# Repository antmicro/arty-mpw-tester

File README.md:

# Arty MPW Tester

Copyright (c) 2022-2025 [Antmicro](https://www.antmicro.com)

### Overview

This repository contains open hardware design files for a simple expansion board compatible with [Digilent Arty A7](https://digilent.com/shop/arty-a7-artix-7-fpga-development-board/) development kit.
This board connects IO signals from the Xilinx Artix FPGA located on the Arty board to an open hardware [Caravel](https://github.com/efabless/caravel_board) breakout board.
The Caravel breakout board allows testing ASIC designs prepared for Multi Project Wafer (MPW) shuttles and fabricated with one of the available open Process Design Kits (PDKs).

You can learn more about Open Shuttle Program by visiting this [link](https://efabless.com/open_shuttle_program).

The Arty MPW Tester board routes the interfaces from Caravel and provides the necessary power buses.
The design files were prepared in KiCad 9.

## Repository structure

The main repository directory contains KiCad PCB project files, a [LICENSE](LICENSE), and a README.
The remaining files are stored in the following directories:

* `doc` - contains generated documentation
* `img` - contains graphics for this README

## Key features

* Caravel-breakout testbed slot with optional FlexyPins
* Arty A7 chipKIT compatible
* USB for MPRJ SPI/UART debug
* SPI Flash connected to Caravel and Arty
* Dedicated 10MHz oscillator
* Dual LDO with fixed and I2C controlled feedback (selectable)
* 37 MPRJ_IO, clock input, GPIO and reset connected to chipKIT header
* Pin headers for all power rails, reset, clock, UART and SPI Flash

## Licensing

This project is published under the [Apache-2.0](LICENSE) License.

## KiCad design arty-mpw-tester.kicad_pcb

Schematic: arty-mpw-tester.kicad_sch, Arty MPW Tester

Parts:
C1, C3, C22, C23, C24, C26, C27, C28, C29, C30, C31, C32, C35, C36: C_1u_0603; 0603-cap; MPN 0603YD105KAT2A
C2, C4, C19, C20, C21, C25, C33, C34, C37: C_100n_0603; 0603-cap; MPN 0603YC104KAZ2A
D3, D4: KP-1608ZGC; LED_0603; MPN KP-1608EC
D6, D9: PMEG6002EJ,115; SOD-323F; MPN PMEG6002EJ,115
D7, D8: 1N5819HW-7-F; SOD-123; MPN 1N5819HW-7-F
J3: arty_chipKIT_connector; ARTY_A7_SHIELD; MPN 9-146281-0
J4, J6, J7, J8, J9, J10, J11, J12: 61300211121; PinHeader_1x2_P2.54_Drill0.9mm; MPN 61300211121
J5, J14, J15: 61300311121; PinHeader_1x3_P2.54_Drill1.1mm; MPN 61300311121
J18, J20: 61300411121; PinHeader_1x4_P2.54mm_Drill1.02mm; MPN 61300411121
J19: 61300711121; MPN 61300711121
NT1, NT2, NT3, NT4, NT5, NT6, NT7, NT8, NT9, NT10, NT11, NT12, NT13, NT14: NetTie_2; NetTie-2_SMD_Pad0.15mm
Q1: DTC014TEBTL; SOT-416; MPN DTC014TEBTL
R1, R9, R10, R38, R39, R40, R41: R_0R01_1206; 1206-res; MPN RL1206FR-7W0R01L
R8, R11, R14, R15, R29, R35: R_0R_0603; 0603-res; MPN CR0603-J/-000ELF
R12, R13: R_470R_0603; 0603-res; MPN CR0603-JW-471GLF
R16, R17, R18, R19, R20, R21, R26, R28, R30, R32, R33, R34, R36, R37: R_10k_0603; 0603-res; MPN CR0603-JW-103ELF
R22: R_68k_0603; 0603-res; MPN MC0063W0603168K
R23: R_41k2_0603; 0603-res; MPN CRCW060341K2FKEA
R24: R_15k_0603; 0603-res; MPN CR0603-FX-1502ELF
R25: R_34k_0603; 0603-res; MPN ERJ-3EKF3402V
R27, R31: R_4k7_0603; 0603-res; MPN CR0603-FX-4701ELF
S1: KMR2; SW_SPST_4.2x2.8; MPN KMR211NGLFS
SW1, SW3: JS202011JCQN; MPN JS202011JCQN
TP1: RCW-0C; PROBE_PAD_1206; MPN RCW-0C
U1, U3: PAC1954T-E/4MX; VQFN-16-1EP_3x3mm_P0.5mm_EP1.1x1.1mm; MPN PAC1954T-E/4MX
U4: MAX811REUS+T; SOT-143-4; MPN MAX811REUS+T
U5: NTS0102DP; TSSOP-8_W3mm; MPN NTS0102DP
U6: MCP4661-103E/ML; QFN-16_EP_4x4_Pitch0.65mm; MPN MCP4661103E/ML
U7: Caravel_breakout_PCB_flexypin; caravel-breakout-flexypin
U8: W25Q32FVSS; SOIC127P790X216-8N; MPN W25Q32FVSSIG
U9: MIC2211-AAYML-TR; DFN-10-1EP_3x3mm; MPN MIC2211-AAYML-TR
Y2: ECS-2520MVLC-100-BN-TR; Oscillator_SMD_ECS_2520MV-xxx-xx-4Pin_2.5x2.0mm; MPN ECS-2520MVLC-100-BN-TR

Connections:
3V3_FTDI: C2.1, C4.1, R36.1, R37.1, U1.2 (VDD), U3.2 (VDD), U3.6 (ADDRSEL); also elsewhere on the board
+1V8: C36.1, J10.1, J11.1, J12.1, R24.2, R26.2, U9.9 (VOUT2)
+3V3: C19.1, C20.1, C34.1, C35.1, D3.1, D4.1, J6.1, J7.1, J8.1, J9.1, R16.2, R17.1, R18.1, R19.1, R21.1, R22.2, R28.1, R32.1, R34.1, U4.4 (VCC), U8.8 (VCC), U9.10 (VOUT1), Y2.4 (VDD)
/3V3_ARTY: C1.1, C21.1, J3.4 (3V3), U5.3 (VCC_A), U5.6 (OE)
/5V0: C25.1, C32.1, C37.1, D7.K, D8.K, R20.1, R27.2, R30.1, R31.2, R33.1, U5.7 (VCC_B), U6.15 (VDD), U9.1 (VIN)
/5V0_ARTY: C3.1, D8.A, J3.5 (5V), SW3.2 (1_C), SW3.6 (2_C)
/ARTY_EN_VOUT1: J3.9 (A0), SW1.1
/ARTY_EN_VOUT2: J3.19 (A6), SW1.5
/ARTY_MEM_CS: J3.25 (SS), R8.1
/ARTY_MEM_MISO: J3.28 (MISO), R14.1
/ARTY_MEM_MOSI: J3.29 (MOSI), R15.1
/ARTY_MEM_SCK: J3.27 (SCK), R11.1
/ARTY_SCL: R31.1, U5.8 (B1), U6.1 (SCL)
/ARTY_SCL_3V3: J3.47 (SCL), U1.4 (SM_CLK), U3.4 (SM_CLK), U5.5 (A1)
/ARTY_SDA: R27.1, U5.1 (B2), U6.2 (SDA)
/ARTY_SDA_3V3: J3.48 (SDA), U1.5 (SM_DATA), U3.5 (SM_DATA), U5.4 (A2)
/ARTY_XCLK: J3.32 (IO40), J5.3
/ARTY_~MR: D9.K, J3.31 (IO41)
/BYP: C33.1, U9.4 (BYP)
/CRVL_GPIO: J20.2, Q1.1 (B), R35.1, U7.47 (GPIO)
/CRVL_XCLK: J5.2, J20.3, U7.52 (XCLK)
/CRVL_~RST: J20.4, R34.2, U4.2 (~RST), U7.53 (~RST)
/EN_VOUT1: R33.2, SW1.2 (1_C), U9.2 (EN1)
/EN_VOUT2: R30.2, SW1.6 (2_C), U9.3 (EN2)
/HVC: R29.2, U6.16 (HVC/A0)
/LV_BOOSTER: J15.3, R26.1
/P0A: J14.2, R22.1, U6.8 (P0A)
/P0B: J14.1, R23.2, U6.10 (P0B)
/P0W: U6.9 (P0W), U9.5 (ADJ1)
/P1A: J15.2, R24.1, U6.7 (P1A)
/P1B: J15.1, R25.2, U6.5 (P1B)
/P1W: U6.6 (P1W), U9.7 (ADJ2)
/VCCD: C28.1, C31.1, NT12.2, R41.2, U7.6 (VCCD), U7.50 (VCCD)
/VCCD1: C24.1, NT13.2, R9.2, U7.43 (VCCD1)
/VCCD1_SEN_+: NT6.1, U3.11 (IN1+)
/VCCD1_SEN_-: NT13.1, U3.12 (IN1-)
/VCCD2: C22.1, NT14.2, R10.2, U7.56 (VCCD2)
/VCCD2_SEN_+: NT7.1, U3.13 (IN2+)
/VCCD2_SEN_-: NT14.1, U3.14 (IN2-)
/VCCD_SEN_+: NT5.1, U3.8 (IN3+)
/VCCD_SEN_-: NT12.1, U3.7 (IN3-)
/VDDA: C30.1, NT9.2, R38.2, U7.45 (VDDA)
/VDDA1: C27.1, NT10.2, R39.2, U7.44 (VDDA1)
/VDDA1_SEN_+: NT3.1, U1.11 (IN1+)
/VDDA1_SEN_-: NT10.1, U1.12 (IN1-)
/VDDA2: C23.1, NT11.2, R40.2, U7.54 (VDDA2)
/VDDA2_SEN_+: NT4.1, U1.10 (IN4+)
/VDDA2_SEN_-: NT11.1, U1.9 (IN4-)
/VDDA_SEN_+: NT2.1, U1.13 (IN2+)
/VDDA_SEN_-: NT9.1, U1.14 (IN2-)
/VDDIO: C26.1, C29.1, J18.1, NT8.2, R1.2, U7.7 (VDDIO), U7.55 (VDDIO)
/VDDIO_SEN_+: NT1.1, U1.8 (IN3+)
/VDDIO_SEN_-: NT8.1, U1.7 (IN3-)
/XCLK_10MHz: J5.1, Y2.3 (OUT)
/XCLK_EN: J4.1, R16.1, Y2.1 (EN)
/~MR: D6.A, D9.A, S1.1, S1.3, U4.3 (~MR)
/~WP: R20.2, U6.12 (~WP)
CRVL_IO0: J3.33 (IO39), U7.42 (IO0)
CRVL_IO1: J3.51 (IO13), U7.41 (SDO_IO1); also elsewhere on the board
CRVL_IO2: J3.34 (IO38), U7.40 (SDI_IO2); also elsewhere on the board
CRVL_IO3: J3.52 (IO12), U7.39 (~CS_IO3); also elsewhere on the board
CRVL_IO4: J3.35 (IO37), U7.38 (SCK_IO4); also elsewhere on the board
CRVL_IO5: J3.53 (IO11), J18.2, U7.37 (RX_IO5); also elsewhere on the board
CRVL_IO6: J3.36 (IO36), J18.3, U7.36 (TX_IO6); also elsewhere on the board
CRVL_IO7: J3.54 (IO10), U7.35 (IO7)
CRVL_IO8: J3.37 (IO35), U7.34 (IO8)
CRVL_IO9: J3.55 (IO09), U7.33 (IO9)
CRVL_IO10: J3.38 (IO34), U7.32 (IO10)
CRVL_IO11: J3.56 (IO08), U7.31 (IO11)
CRVL_IO12: J3.39 (IO33), U7.30 (IO12)
CRVL_IO13: J3.57 (IO07), U7.29 (IO13)
CRVL_IO14: J3.40 (IO32), U7.28 (IO14)
CRVL_IO15: J3.58 (IO06), U7.27 (IO15)
CRVL_IO16: J3.41 (IO31), U7.26 (IO16)
CRVL_IO17: J3.59 (IO05), U7.25 (IO17)
CRVL_IO18: J3.42 (IO30), U7.24 (IO18)
CRVL_IO19: J3.60 (IO04), U7.23 (IO19)
CRVL_IO20: J3.43 (IO29), U7.22 (IO20)
CRVL_IO21: J3.61 (IO03), U7.21 (IO21)
CRVL_IO22: J3.44 (IO28), U7.20 (IO22)
CRVL_IO23: J3.62 (IO02), U7.19 (IO23)
CRVL_IO24: J3.45 (IO27), U7.18 (IO24)
CRVL_IO25: J3.63 (IO01), U7.17 (IO25)
CRVL_IO26: J3.46 (IO26), U7.16 (IO26)
CRVL_IO27: J3.64 (IO00), U7.15 (IO27)
CRVL_IO28: J3.24 (A11), U7.14 (IO28)
CRVL_IO29: J3.14 (A5), U7.13 (IO29)
CRVL_IO30: J3.23 (A10), U7.12 (IO30)
CRVL_IO31: J3.13 (A4), U7.11 (IO31)
CRVL_IO32: J3.22 (A9), U7.10 (IO32)
CRVL_IO33: J3.12 (A3), U7.9 (IO33)
CRVL_IO34: J3.21 (A8), U7.4 (IO34)
CRVL_IO35: J3.11 (A2), U7.3 (IO35)
CRVL_IO36: J3.20 (A7), U7.2 (IO36)
CRVL_IO37: J3.10 (A1), U7.1 (IO37)
EP: C1.2, C2.2, C3.2, C4.2, C19.2, C20.2, C21.2, C22.2, C23.2, C24.2, C25.2, C26.2, C27.2, C28.2, C29.2, C30.2, C31.2, C32.2, C33.2, C34.2, C35.2, C36.2, C37.2, J3.6 (GND), J3.7 (GND), J3.17 (XGND), J3.26 (GND), J3.50 (GND), J4.2, J18.4, J19.7, J20.1, Q1.2 (E), R13.1, R23.1, R25.1, R29.1, S1.2, S1.4, TP1.1, U1.1 (SLOW/~ALERT), U1.3 (GND), U1.6 (ADDRSEL), U1.15 (GPIO/~ALERT2), U1.17 (EP), U3.1 (SLOW/~ALERT), U3.3 (GND), U3.15 (GPIO/~ALERT2), U3.17 (EP), U4.1 (GND), U5.2 (GND), U6.3 (VSS), U6.4 (VSS), U6.13 (A2), U6.14 (A1), U6.17 (EP), U7.5 (GND), U7.8 (GND), U8.4 (GND), U9.6 (GND), U9.11 (EP), Y2.2 (GND); also elsewhere on the board
FTDI_EN_VOUT1: SW1.3; also elsewhere on the board
FTDI_EN_VOUT2: SW1.7; also elsewhere on the board
FTDI_~MR: D6.K; also elsewhere on the board
MEM.SCK: J19.2, R11.2, R18.2, U7.46 (FLASH_SCK), U8.6 (SCK); also elsewhere on the board
MEM.SI: J19.3, R15.2, R19.2, U7.49 (FLASH_D0), U8.5 (SI(D0)); also elsewhere on the board
MEM.SO: J19.4, R14.2, R21.2, U7.48 (FLASH_D1), U8.2 (SO(D1)); also elsewhere on the board
MEM.~CS: J19.1, R8.2, R17.2, U7.51 (~FLASH_CS), U8.1 (~CS); also elsewhere on the board
MEM.~HOLD: J19.6, R32.2, U8.7 (~HOLD(D3))
MEM.~WP: J19.5, R28.2, U8.3 (~WP(D2))
unnamed: D3.2, R12.2
unnamed: D4.2, R13.2
unnamed: J3.49 (IO42), R35.2
unnamed: J6.2, NT2.2, R38.1
unnamed: J7.2, NT1.2, R1.1
unnamed: J8.2, NT4.2, R40.1
unnamed: J9.2, NT3.2, R39.1
unnamed: J10.2, NT5.2, R41.1
unnamed: J11.2, NT6.2, R9.1
unnamed: J12.2, NT7.2, R10.1
unnamed: Q1.3 (C), R12.1
unnamed: R36.2, U1.16 (~PWRDN)
unnamed: R37.2, U3.16 (~PWRDN)
VBUS: D7.A, SW3.3, SW3.7; also elsewhere on the board

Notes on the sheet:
SERIAL
CRVL_RX
Dynamic 3V3 Fixed
SMBus/I2C Address 0010 000 (R/W)
Caravel Shunt resistors
Configurable LDO
GND TEST POINT
Note: internal 10k I2C pullups in NTS0102
GPIO, XCLK, ~{RST}
Flash memory
MEMS Oscillator
ARTY A7 connectors
Dynamic 1V8 Fixed
SCK
Caravel breakout PCB
CRVL_TX
POWER LED
Caravel Power Monitors
ARTY_TX
FTDI Module
OSCILLATOR DISABLE
Configurable feedback
ARTY_RX
Reset
Signal breakouts
MOSI
XCLK SELECT
Optional Arty A7 Interface with FLASH
MEMORY
VBUS to Arty 5.0V connection
MISO
SMBus/I2C Address 0011 111 (R/W)
USR LED
CS1

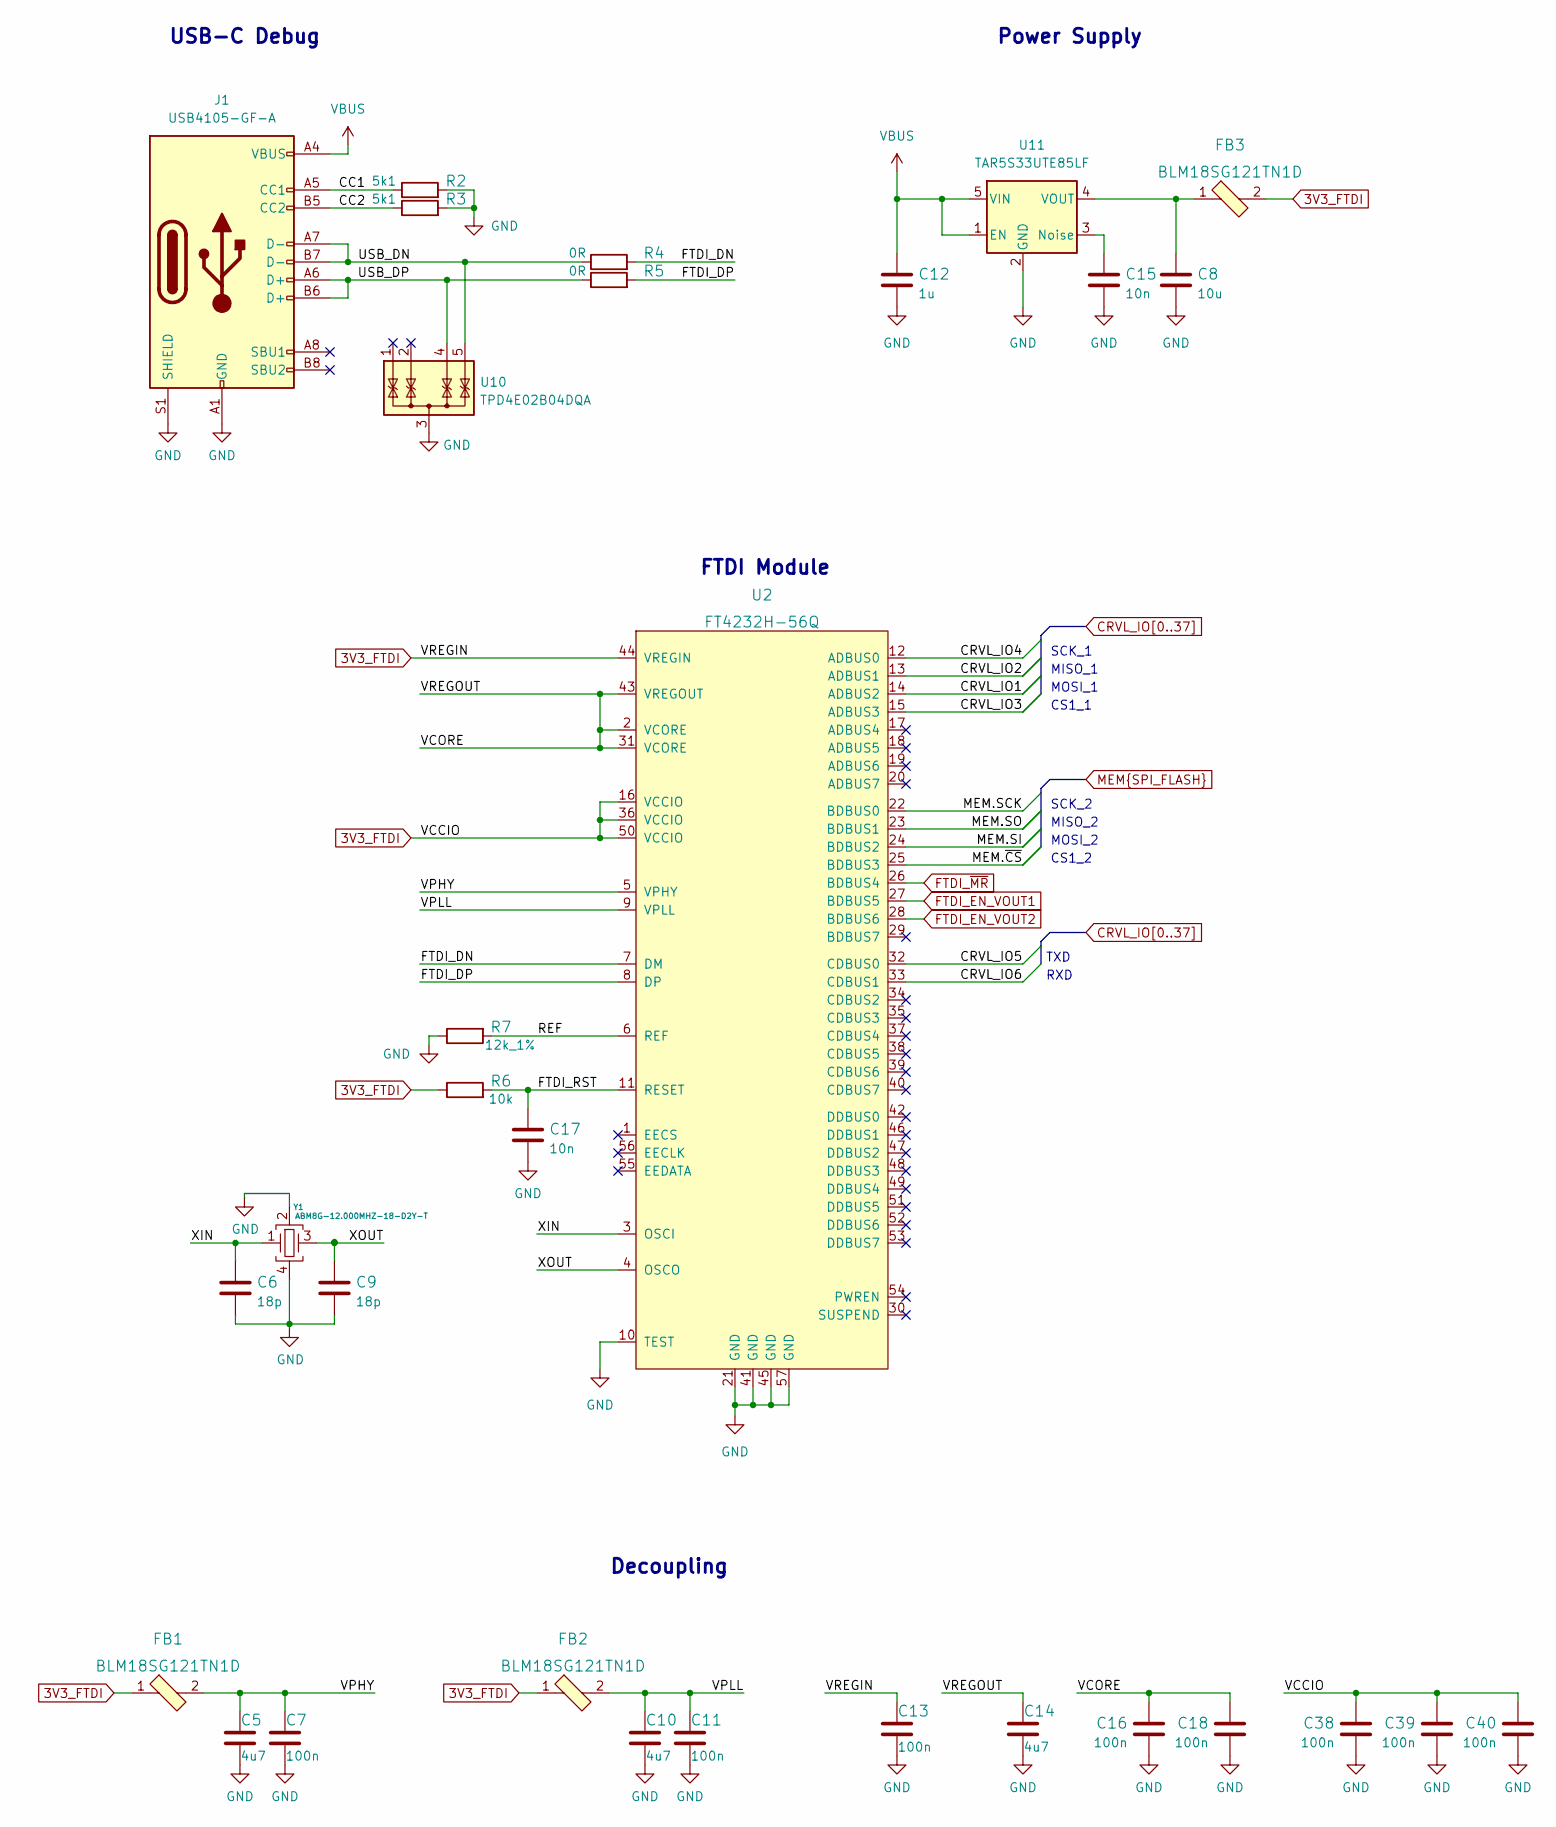
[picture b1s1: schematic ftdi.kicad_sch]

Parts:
C5, C10, C14: C_4u7_0603; 0603-cap; MPN C1608X5R1V475M080AC
C6, C9: C_18p_0603; 0603-cap; MPN C0603C180J5GACTU
C7, C11, C13, C16, C18, C38, C39, C40: C_100n_0603; 0603-cap; MPN 0603YC104KAZ2A
C8: C_10u_0603; 0603-cap; MPN GRM188R61A106KE69D
C12: C_1u_0603; 0603-cap; MPN 0603YD105KAT2A
C15, C17: C_10n_0603; 0603-cap; MPN 06031C103JAT2A
FB1, FB2, FB3: BLM18SG121TN1D; 0603-res; MPN BLM18SG121TN1D
J1: USB4105-GF-A; GCT_USB4105-GF-A; MPN USB4105-GF-A
R2, R3: R_5k1_0603; 0603-res; MPN CRCW06035K10FKEA
R4, R5: R_0R_0402; 0402-res; MPN ERJ2GE0R00X
R6: R_10k_0603; 0603-res; MPN CR0603-JW-103ELF
R7: R_12k_1%_0603; 0603-res; MPN MCWR06X1202FTL
U2: FT4232H-56Q; QFN-56-1EP_8x8mm_P0.5mm_EP5.5.9x5.9mm; MPN FT4232H-56Q-REEL
U10: TPD4E02B04DQA; USON-10_2.5x1.0mm_P0.5mm; MPN TPD4E02B04DQAR
U11: TAR5S33UTE85LF; SOT-353; MPN TAR5S33UTE85LF
Y1: ABM8G-12.000MHZ-18-D2Y-T; KX-7; MPN ABM8G-12.000MHZ-18-D2Y-T

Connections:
3V3_FTDI: C13.1, C38.1, C39.1, C40.1, FB1.1, FB2.1, FB3.2, R6.1, U2.16 (VCCIO), U2.36 (VCCIO), U2.44 (VREGIN), U2.50 (VCCIO); also elsewhere on the board
/FTDI/CC1: J1.A5 (CC1), R2.1
/FTDI/CC2: J1.B5 (CC2), R3.1
/FTDI/FTDI_DN: R4.2, U2.7 (DM)
/FTDI/FTDI_DP: R5.2, U2.8 (DP)
/FTDI/FTDI_RST: C17.1, R6.2, U2.11 (RESET)
/FTDI/REF: R7.2, U2.6 (REF)
/FTDI/USB_DN: J1.A7 (D-), J1.B7 (D-), R4.1, U10.5 (IO4), U10.6 (NC)
/FTDI/USB_DP: J1.A6 (D+), J1.B6 (D+), R5.1, U10.4 (IO3), U10.7 (NC)
/FTDI/VCORE: C14.1, C16.1, C18.1, U2.2 (VCORE), U2.31 (VCORE), U2.43 (VREGOUT)
/FTDI/VPHY: C5.1, C7.1, FB1.2, U2.5 (VPHY)
/FTDI/VPLL: C10.1, C11.1, FB2.2, U2.9 (VPLL)
/FTDI/XIN: C6.1, U2.3 (OSCI), Y1.1
/FTDI/XOUT: C9.1, U2.4 (OSCO), Y1.3
CRVL_IO1: U2.14 (ADBUS2); also elsewhere on the board
CRVL_IO2: U2.13 (ADBUS1); also elsewhere on the board
CRVL_IO3: U2.15 (ADBUS3); also elsewhere on the board
CRVL_IO4: U2.12 (ADBUS0); also elsewhere on the board
CRVL_IO5: U2.32 (CDBUS0); also elsewhere on the board
CRVL_IO6: U2.33 (CDBUS1); also elsewhere on the board
EP: C5.2, C6.2, C7.2, C8.2, C9.2, C10.2, C11.2, C12.2, C13.2, C14.2, C15.2, C16.2, C17.2, C18.2, C38.2, C39.2, C40.2, J1.A1 (GND), J1.A12 (GND), J1.B1 (GND), J1.B12 (GND), J1.S1 (SHIELD), R2.2, R3.2, R7.1, U2.10 (TEST), U2.21 (GND), U2.41 (GND), U2.45 (GND), U2.57 (GND), U10.3 (G), U10.8 (G), U11.2 (GND), Y1.2, Y1.4; also elsewhere on the board
FTDI_EN_VOUT1: U2.27 (BDBUS5); also elsewhere on the board
FTDI_EN_VOUT2: U2.28 (BDBUS6); also elsewhere on the board
FTDI_~MR: U2.26 (BDBUS4); also elsewhere on the board
MEM.SCK: U2.22 (BDBUS0); also elsewhere on the board
MEM.SI: U2.24 (BDBUS2); also elsewhere on the board
MEM.SO: U2.23 (BDBUS1); also elsewhere on the board
MEM.~CS: U2.25 (BDBUS3); also elsewhere on the board
unnamed: C8.1, FB3.1, U11.4 (VOUT)
unnamed: C15.1, U11.3 (Noise)
VBUS: C12.1, J1.A4 (VBUS), J1.A9 (VBUS), J1.B4 (VBUS), J1.B9 (VBUS), U11.1 (EN), U11.5 (VIN); also elsewhere on the board

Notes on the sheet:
MOSI_2
TXD
USB-C Debug
CS1_1
CS1_2
MOSI_1
FTDI Module
RXD
Power Supply
MISO_2
SCK_1
MISO_1
Decoupling
SCK_2

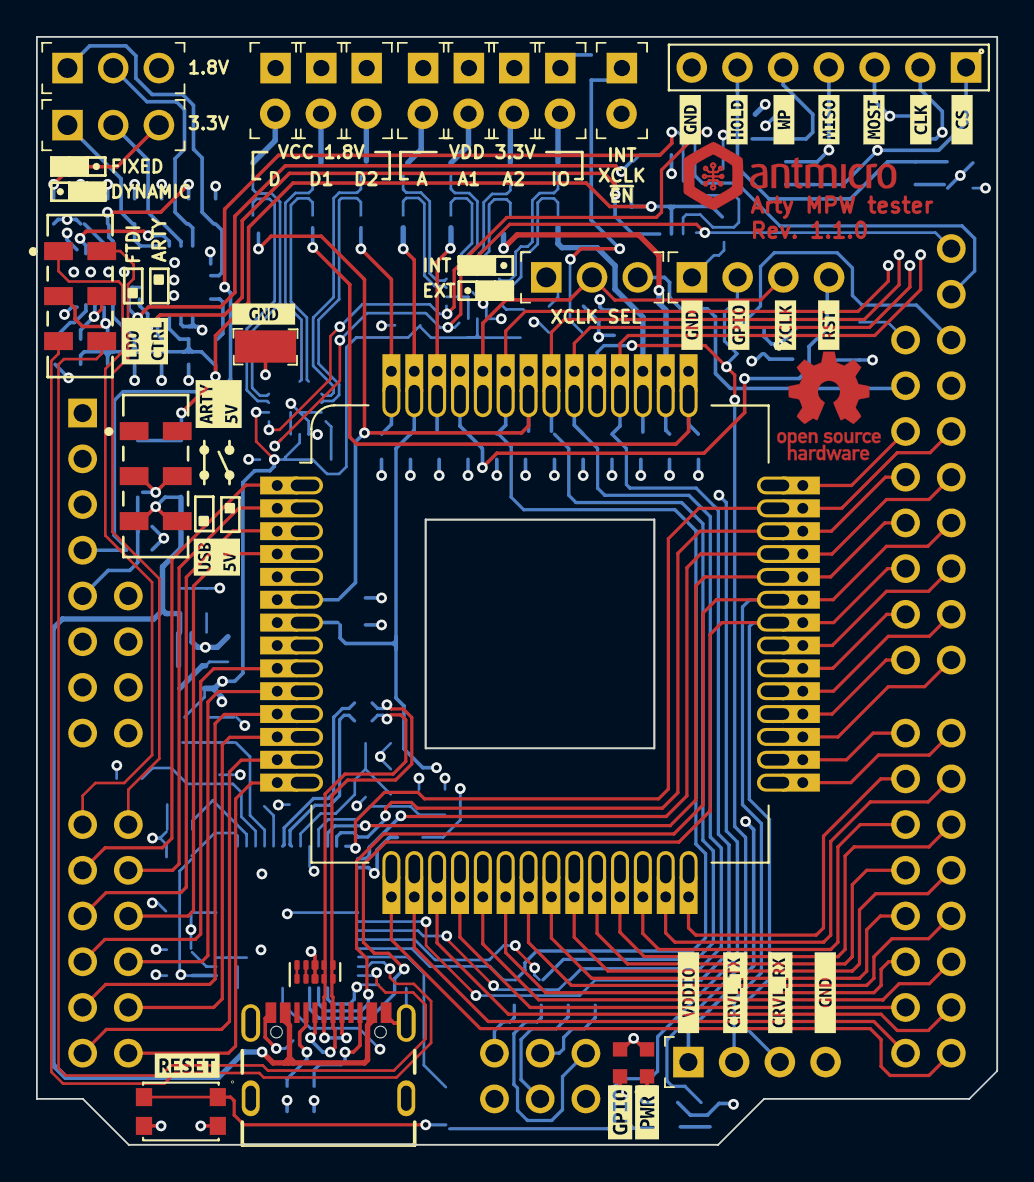
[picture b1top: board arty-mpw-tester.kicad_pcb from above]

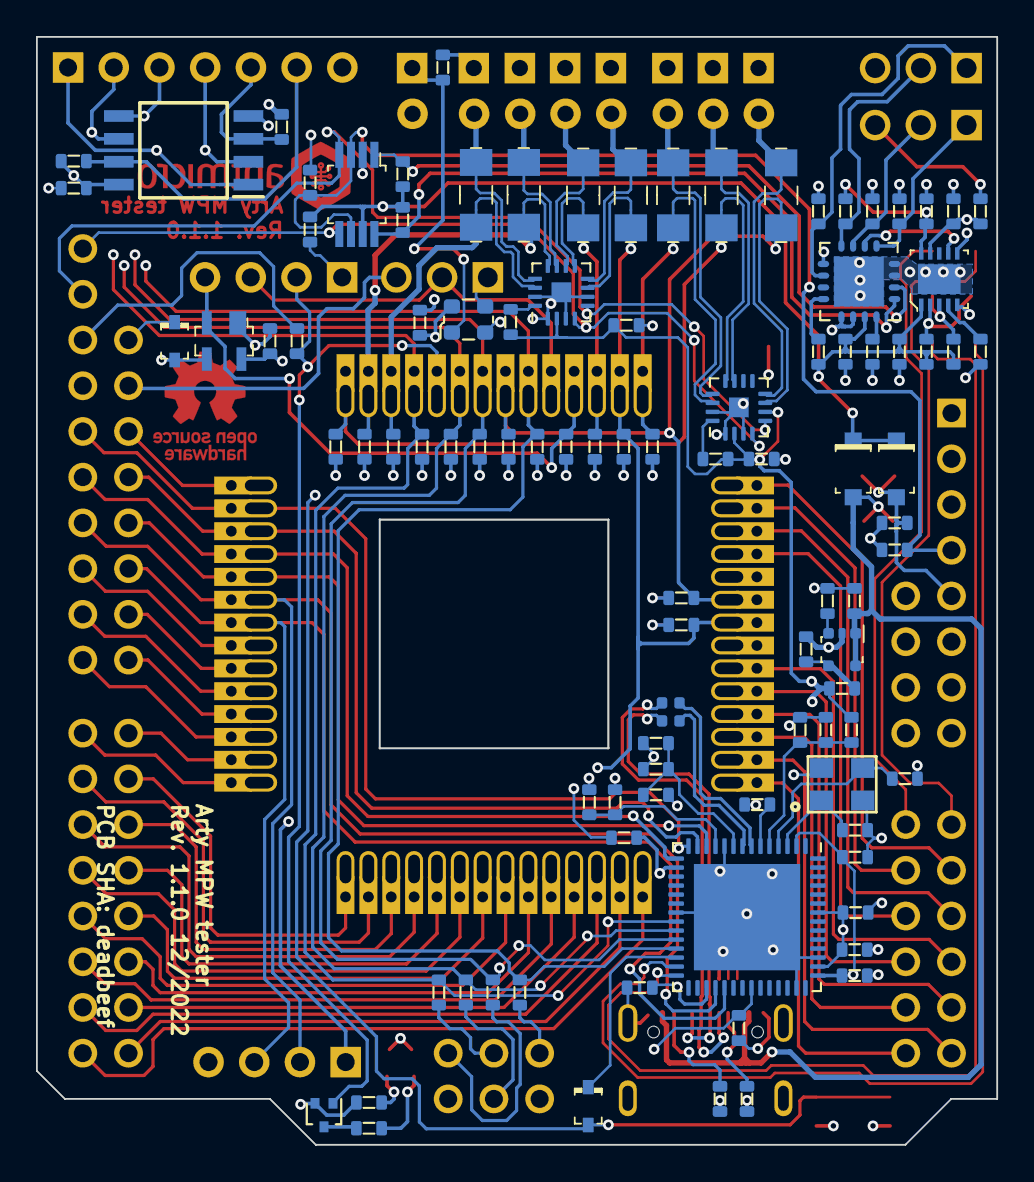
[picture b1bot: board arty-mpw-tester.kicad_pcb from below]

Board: 4 copper layers, 53.3 x 61.5 mm, 160 parts (115 on the bottom side), 134 nets.

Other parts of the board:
kibuzzard-638F9F6E: G***; kibuzzard-638F9F6E
kibuzzard-638F9F51: G***; kibuzzard-638F9F51
kibuzzard-638F9F83: G***; kibuzzard-638F9F83
kibuzzard-638FA1CB: G***; kibuzzard-638FA1CB
kibuzzard-63938A8C: G***; kibuzzard-63938A8C
kibuzzard-639040B1: G***; kibuzzard-639040B1
kibuzzard-639040B6: G***; kibuzzard-639040B6
kibuzzard-639040BB: G***; kibuzzard-639040BB
kibuzzard-639040CA: G***; kibuzzard-639040CA
kibuzzard-639091D1: G***; kibuzzard-639091D1
kibuzzard-639091D4: G***; kibuzzard-639091D4
kibuzzard-639091D8: G***; kibuzzard-639091D8
kibuzzard-639091DC: G***; kibuzzard-639091DC
kibuzzard-639390A2: G***; kibuzzard-639390A2
kibuzzard-6390923A: G***; kibuzzard-6390923A
kibuzzard-6390923D: G***; kibuzzard-6390923D
kibuzzard-6393906F: G***; kibuzzard-6393906F
kibuzzard-63909224: G***; kibuzzard-63909224
kibuzzard-63909228: G***; kibuzzard-63909228
kibuzzard-63909232: G***; kibuzzard-63909232
kibuzzard-63909236: G***; kibuzzard-63909236
kibuzzard-63909242: G***; kibuzzard-63909242

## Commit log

2022-12-02 Add FTDI and USB. Improve Caravel breakout symbol
2022-12-02 Add voltage selection, add current measurement points add UART buffer
2022-12-02 Add LDOs and 10MHz oscillator
2022-12-02 Add remaining ICs, divide schematic into blocks. Add Arty A7 hat outline
2022-12-05 Unify labels
2022-12-05 Add decoupling to the Caravel
2022-12-05 Improve FTDI symbol. Udpate LDO EN signal name scheme
2022-12-05 Simplify power section. Add header to each Caravel power rail
2022-12-05 Update MCP4661 symbol
2022-12-05 Cleanup net names
2022-12-05 Cleanup configurable LDO section
2022-12-05 Replace 0603 and 0805 100n and 18p capacitors with 0402
2022-12-05 Inital placement
2022-12-06 Improve placement, aling pin headers
2022-12-06 Start connecting Caravel to Arty
2022-12-06 Fix signals label on U3. Power U3 from FTDI 3V3
2022-12-06 Update project settings
2022-12-06 Connect Caravel after rotating it on PCB. Adjust component placement
2022-12-06 Add labels
2022-12-07 Remove dimmensions used to center the Caravel module
2022-12-07 Use appropriate resistor values in LDO feedback, simplify power section
2022-12-07 Import changes to PCB, adjust placement
2022-12-07 Change R/C components to 0603 package. Change I2C translator package
2022-12-07 Replace remaining 0402 components with 0603 except resistors on USB_D lines
2022-12-07 Import changes to PCB. Adjust placement. Partial layout
2022-12-07 Improve placement of the pin headers
2022-12-07 Connect remaining singals to Arty
2022-12-07 Start power section layout. Adjust J6-J12 position on schematic to resolve crosses on PCB
2022-12-08 Change page size to A3, add diodes to buffer UART_EN and MR signals
2022-12-08 Fix label names
2022-12-08 Import changes to PCB, place new diodes
2022-12-08 Improve readability of the MR and UART_EN connections
2022-12-08 Add LDO EN signals switch between ARTY and FTDI
2022-12-08 Add PWR CTRL switch to the PCB, place UART selector in TMP place
2022-12-08 correct too small footprint of FTDI, reconnect nearby tracks
2022-12-08 Remove EP vias from FT232 footprint
2022-12-09 Update FT232H footprint
2022-12-09 Swap Arty_EN_VOUT 1 and 2. Continue layout
2022-12-09 Finish routing of the board without UART_EN header
2022-12-09 Add slide switches for Arty powered from USB and UART buffer ctrl
2022-12-09 Add USB TVS, finish layout, resolve DRC
2022-12-09 Loclib
2022-12-12 Update footprints, add missing 3D models
2022-12-12 Fix Arty symbol, add EP pin to MIC221 and MCP4661 symbols
2022-12-12 Update footprints, add courtyard to Arty connectors, minor layout optimizations
2022-12-12 Update Caravel footprint
2022-12-12 Add logos to the schematic
2022-12-12 Add logos and marking
2022-12-12 correct MPN of arty connector
2022-12-12 Add PCB marking, fix footprint types, update layout
2022-12-12 correct arty connector symbol in local lib
2022-12-12 Exclude silkscreen violations
2022-12-12 Add license
2022-12-12 Add optional connection between Arty IO42 and Caravel GPIO
2022-12-12 Add readme
2022-12-12 Added model of Arty A7 fof visualization. Corrected Antmicro logo
2022-12-12 Unify designator and values, hide them
2022-12-12 Removed Arty A7 model
2022-12-12 Corrected deadbeef signage
2022-12-12 Fix signage
2022-12-12 Update naming convention
2022-12-12 Fix copyright string
2022-12-12 README review
2022-12-12 README: minor fix
2022-12-14 Update caravel-breakout footprint with more detailed 3D model and flexypins
2022-12-14 Rotate slide switches so 3D models match default configuration. Update Arty A7 shield connector side
2022-12-14 Add jumper models to the PCB
2022-12-27 Add documentation stub
2022-12-27 Change "special" to "dedicated" in pinout table
2022-12-27 Clarify note about connecting 5V Atry an 5V USB rails
2022-12-27 Move docs back to doc folder
2022-12-27 Add pinouts to UART, SPI flash and Caravel MGMT headers
2022-12-27 Add pinouts
2022-12-27 Reduced docs requirements
2022-12-27 Fix typos
2022-12-27 Add initial info about configuration, power and xclk
2022-12-27 Add visualization with jumpers
2022-12-27 Remove background from pngs
2022-12-27 Update PCB img
2022-12-27 Add full resolution assets for docs
2022-12-27 DOCS:Add content to USB UART and XCLK section. Update Power section.
2022-12-27 Move readthedocs source files to docs, update naming on the pages
2022-12-27 Improve configuration description
2022-12-27 Exchanged FT232 to FT4232 on schematics
2022-12-27 Renamed FTDI UART to Caravel net after buffers removal
2022-12-27 Add git ignore. Include Auto_saved_files in gitignore
2022-12-27 Added current monitor schematics. Moved FTDI module to separate subsheet
2022-12-27 Adjusted net naming to work in subsheet
2022-12-27 Imported all changes to PCB. Cleared old tracks. Started placement and layout
2022-12-27 Moved and reconnected power supply unit. Placed shunt resistors
2022-12-27 Finished initial routing. Corrected switch footprint
2022-12-27 Cleared DRC. Updated stackup. Optimized paths
2022-12-27 Optimized some paths. orrected power plane under USB tracks
2022-12-27 Adjusted USB TVS position
2022-12-27 Added slight visual adjustments
2022-12-27 Added blendcfg with standard settings
2022-12-27 Added schematic in pdf
2022-12-27 Fix broken symbol after loclib
2022-12-27 Updating docs (WIP)
2022-12-27 Updated documentation after changes
2022-12-27 Update most images
2022-12-27 Updated last images
2022-12-27 Updated image name
2022-12-27 Added block diagram of board
2023-01-06 Add schematic PDF
2023-10-13 Introduce project standardization
2023-10-13 [#50304] Add OHP assets and schematic PDF
2023-10-16 Stop ignoring csv
2024-07-11 [#62395] Perform kmake DNP
2024-07-11 [#62395] Perform kmake globlib
2024-07-11 [#62395] Update symbols D,J,N,Q,SW,U,Y references
2024-07-11 [#62395] Update R,C and allign schematic
2024-07-16 [#62395] Update J2
2024-07-16 [#62395] Update C, D footprints
2024-07-16 [#62395] Update J, N footprints
2024-07-16 [#62395] Update Q,R,S footprints
2024-07-16 [#62395] Update U, Y footprints
2024-07-16 [#62395] Clean ERC
2024-07-16 [#62395] A;;ign designators, fix DRC
2024-07-16 [#62395] Add PCB SHA
2024-07-18 [#62395] Update J4 to M20-9990246
2024-07-18 [#62395] Fix oshw logo coliding silkscreen
2024-07-18 [#62395] Remove loc lib leftovers
2024-07-18 [#62395] Bump rev to 1.1.0
2024-07-18 [#62395] Update date in README
2024-07-18 [#62395] Update GND and 3V3 symbols
2024-07-24 [#62395] Update J6
2024-07-24 [#62395] Fix ERC
2024-07-24 [#62395] Update J2 footprint & fix DRC
2024-07-24 [#62395] Update OHP assets
2024-07-25 [#62395] README: Update copyright and rm WiP status
2024-07-25 [#62395] Schematic: Minor fixes
2024-07-26 [#62395] Add SPI_FLASH bus alias
2024-07-26 [#62395] PCB: Prevent acid traps & update bot rev
2024-07-26 [#62395] Restore docs
2024-07-30 [#62395] Update schematic.pdf
2024-08-09 [#62395] Update assets
2024-08-12 [#62395] Update README img
2024-08-16 [#62395] Update Pin Headers from main comp lib
2024-08-16 [#62395] Refresh pdf
2025-11-19 [#82385] Project refresh 81589
2025-11-19 Fix DNP
2025-11-19 Cleanup files

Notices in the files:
parts and their libraries:
License: MIT
